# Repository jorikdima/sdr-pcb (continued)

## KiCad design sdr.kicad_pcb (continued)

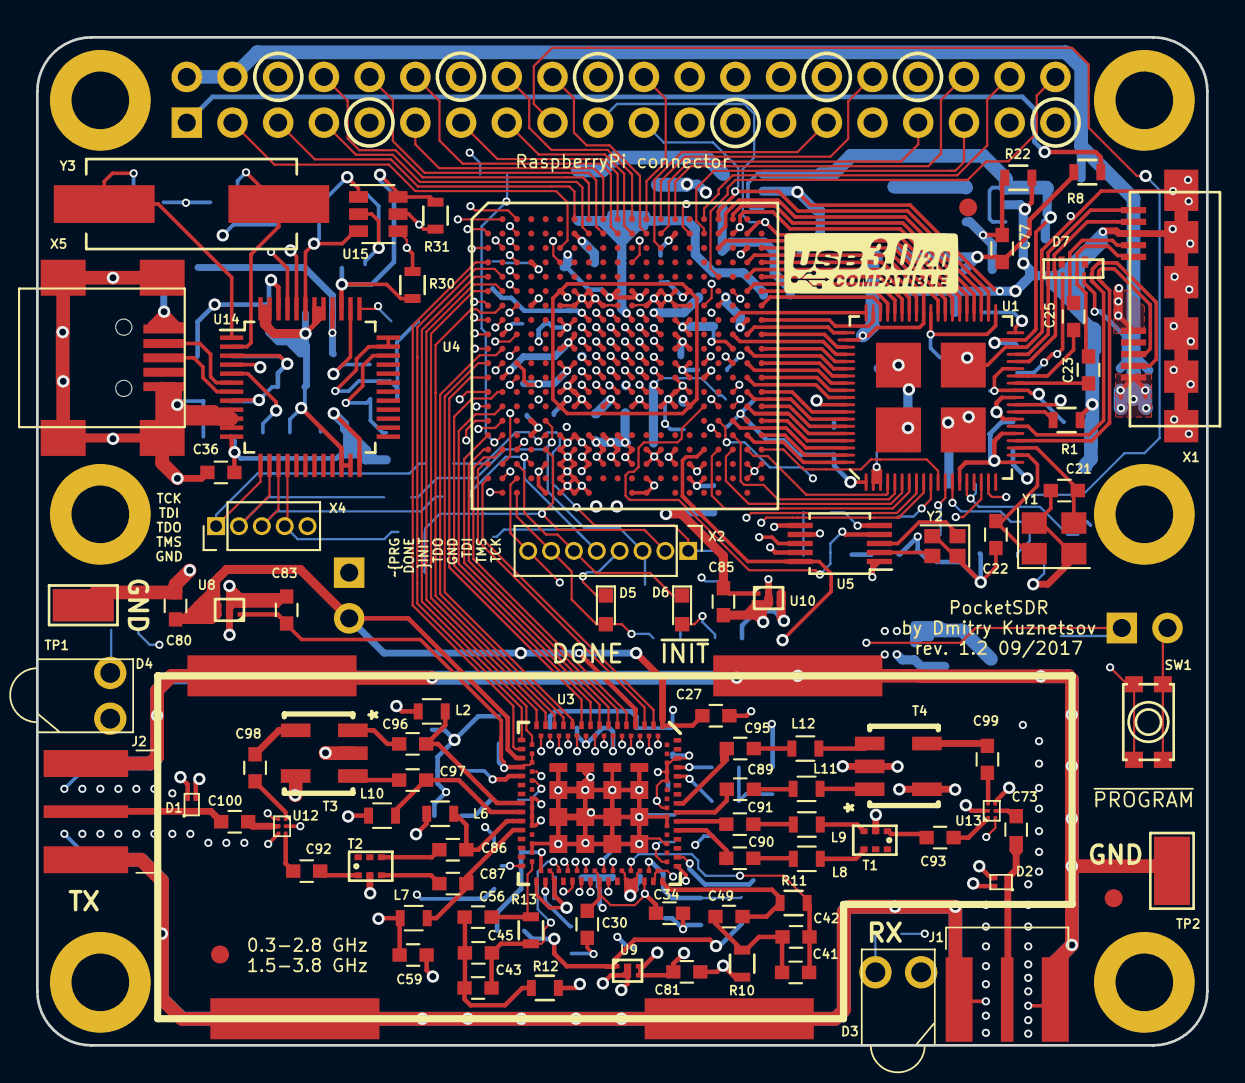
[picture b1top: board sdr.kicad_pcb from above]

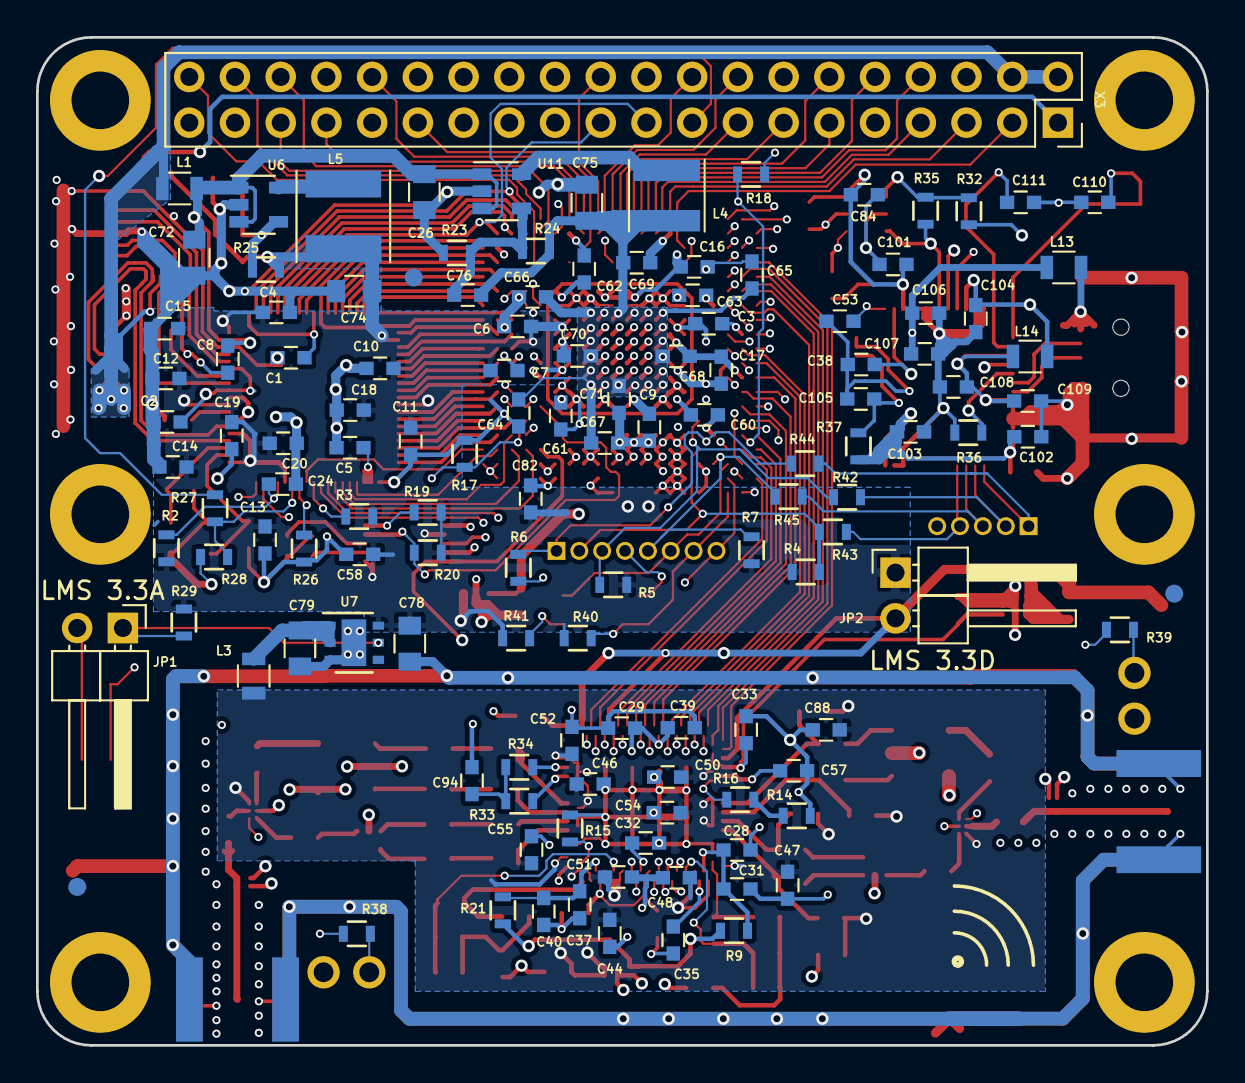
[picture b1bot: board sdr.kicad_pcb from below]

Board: 4 copper layers, 65.0 x 56.0 mm, 211 parts (125 on the bottom side), 223 nets.

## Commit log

2017-02-07 Initial. FTDI schematic is done
2017-02-14 Cloack, LMS are added
2017-02-18 Schematic is done except RF.
2017-02-23 Placed most components for FTDI. Begin tracing FT601
2017-02-23 trace update
2017-02-24 Just before FT_D tracing
2017-03-03 Right before Sitch power retracing
2017-03-03 Power is traced. Placing capacitors for FPGA
2017-03-06 Caps for FPGA are placed. Most of FPGA power is traced. Need to trace Rpi connector
2017-03-07 All traced except Rpi and LMS
2017-03-08 RPI is almost finished
2017-03-10 Everything is done except LMS and RF
2017-03-22 Start placing RF. Shield is ready. Fixed some net bugs.
2017-03-25 Right before switching to full RPi
2017-03-25 Added few files
2017-03-25 Full Rpi beginning
2017-05-17 Fix bug with not traced FT_TXE FT_RXF
2017-05-19 Finish tracing all except SDRAM and AFE
2017-05-23 Changed RF sheet to add second path to TX and RX
2017-05-23 Small changes
2017-05-24 Preliminary placing top layer of RF
2017-05-31 Placement of RF is on going.
2017-06-03 Add jumpers for LMS power Traced most nets in LMS digital
2017-06-04 Placement of all passive is finished. Tracing of most passive is finished. RF is not started yet.
2017-06-06 Fix LMS_3V3A enable pull. Corrected shield ground
2017-06-07 Add schematic of FT232H. Not placed yet.
2017-06-08 Add leds. Traced LMS_3V3A LDO.
2017-06-09 Start tracing IO Fix connector for Rpi Use LED indicator for TX/RX LEDs
2017-06-09 Add VCCIO and some vias
2017-06-10 Finish tracing IO
2017-06-10 Changed couple of pins
2017-06-10 FT232H has been finished Not finished: - PROGRAMN button - silkscreen preparation - RF
2017-06-12 Changed JTAG, added 0 Ohm resistors
2017-06-13 Place RefDes on the top of the board.
2017-06-13 Button is traced. Everything's ready to trace RF.
2017-06-15 Added reference points. Right before RF tracing.
2017-06-16 Finish tracing. No DRC errors or unconnected nets. Put 2.5V reg on the top layer. Need to place RefDes on RF parts.
2017-06-17 Finish silkscreen layer.
2017-06-19 Prepared BOM and changed some part numbers for unpopular ones. Added manufacture PN for each part.
2017-06-19 Changed mask on LMS footprint.
2017-06-19 Fix inductors RefDes silkscreen
2017-06-20 Add logo, rev. GND testpoints etc in silkscreen.
2017-06-20 Fix shield. Added BOM
2017-06-22 Fix shield lines again.
2017-07-21 Start fixing problems with mask size and copper zone clearance.
2017-07-22 Finish fixing problems: 1. LDO 3V3A has been changed as well as it CAPs 2. Silkscreen fixed 3. Mask expansion is changed
2017-07-22 Fix silkscreen of update components. Fix width of fan outs of RF muxers to better soldering.
2017-07-24 Change footprints for LMS and FT601 to allow mask resist between pads. Now only ESD7016 and RF muxers have no mask due to very low pitch.
2017-07-24 Updated solder paste layers. Fix OSC components adding solder paste.
2017-08-10 Update solder paste layer for components. Reduced width of tracks where they were wider than pads. Add mounting holes on paste layers.
2017-08-18 Update solder paste layers to reduce paste amount on some components and remove paste but not drill hole) on mount holes. Updated BOM. Removed deadend line on PCB. Add GND layer on Layer 3.
2017-08-23 Fix USB mini B mount holes.
2017-08-25 Small upgrade to make GND polygon on layer 3 more solid.
2017-08-25 Moved R1 to the same layer as FT600. Rotated Y1.
